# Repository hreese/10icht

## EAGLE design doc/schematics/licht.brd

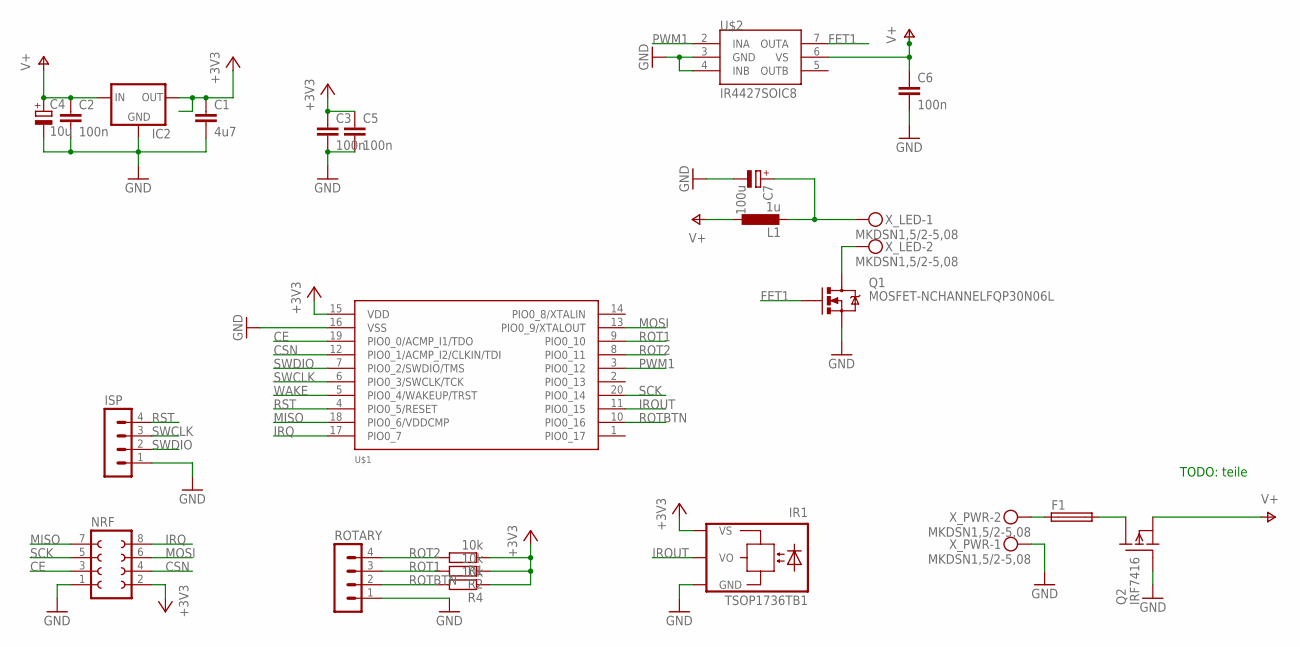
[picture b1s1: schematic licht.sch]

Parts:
C1: 4u7; C0805
C2, C3, C5, C6: 100n; C0805
C4: 10u; E2,5-6
C7: 100u; E2,5-5
F1: PTF45
IC2: TS2940; TO252
IR1: TSOP1736TB1; TSOP17_TB1
ISP: MA04-1
L1: 1u; PISR-BIGPAD
NRF: FE04-2
Q1: MOSFET-NCHANNELFQP30N06L; TO220V
Q2: IRF7416; SO8
R1, R2, R4: 10k; R0805
ROTARY: MA04-1
U$1: LPC812M101JD20; SOIC20WIDE
U$2: IR4427SOIC8; SOIC8
X_LED: MKDSN1,5/2-5,08
X_PWR: MKDSN1,5/2-5,08

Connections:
+3V3: C1.1, C3.1, C5.1, IC2.3 (OUT), IR1.VS, NRF.2, R1.1, R2.1, R4.1, U$1.15 (VDD)
CE: NRF.3, U$1.19 (PIO0_0/ACMP_I1/TDO)
CSN: NRF.4, U$1.12 (PIO0_1/ACMP_I2/CLKIN/TDI)
FET1: Q1.1 (G), U$2.7 (OUTA)
GND: C1.2, C2.2, C3.2, C4.-, C5.2, C6.2, C7.-, IC2.2 (GND), IR1.GND, ISP.1, NRF.1, Q1.3 (S), Q2.4 (G), ROTARY.1, U$1.16 (VSS), U$2.3 (GND), U$2.4 (INB), X_PWR.1
IROUT: IR1.VO, U$1.11 (PIO0_15)
IRQ: NRF.8, U$1.17 (PIO0_7)
MISO: NRF.7, U$1.18 (PIO0_6/VDDCMP)
MOSI: NRF.6, U$1.13 (PIO0_9/XTALOUT)
unnamed: C7.+, L1.2, X_LED.1
unnamed: Q1.2 (D), X_LED.2
unnamed: F1.1, X_PWR.2
unnamed: F1.2, Q2.5 (D), Q2.6 (D), Q2.7 (D), Q2.8 (D)
PWM1: U$1.3 (PIO0_12), U$2.2 (INA)
ROT1: R2.2, ROTARY.3, U$1.9 (PIO0_10)
ROT2: R1.2, ROTARY.4, U$1.8 (PIO0_11)
ROTBTN: R4.2, ROTARY.2, U$1.10 (PIO0_16)
RST: ISP.4, U$1.4 (PIO0_5/RESET)
SCK: NRF.5, U$1.20 (PIO0_14)
SWCLK: ISP.3, U$1.6 (PIO0_3/SWCLK/TCK)
SWDIO: ISP.2, U$1.7 (PIO0_2/SWDIO/TMS)
V+: C2.1, C4.+, C6.1, IC2.1 (IN), L1.1, Q2.1 (S), Q2.2 (S), Q2.3 (S), U$2.6 (VS)
WAKE: U$1.5 (PIO0_4/WAKEUP/TRST)

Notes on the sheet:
TODO: teile

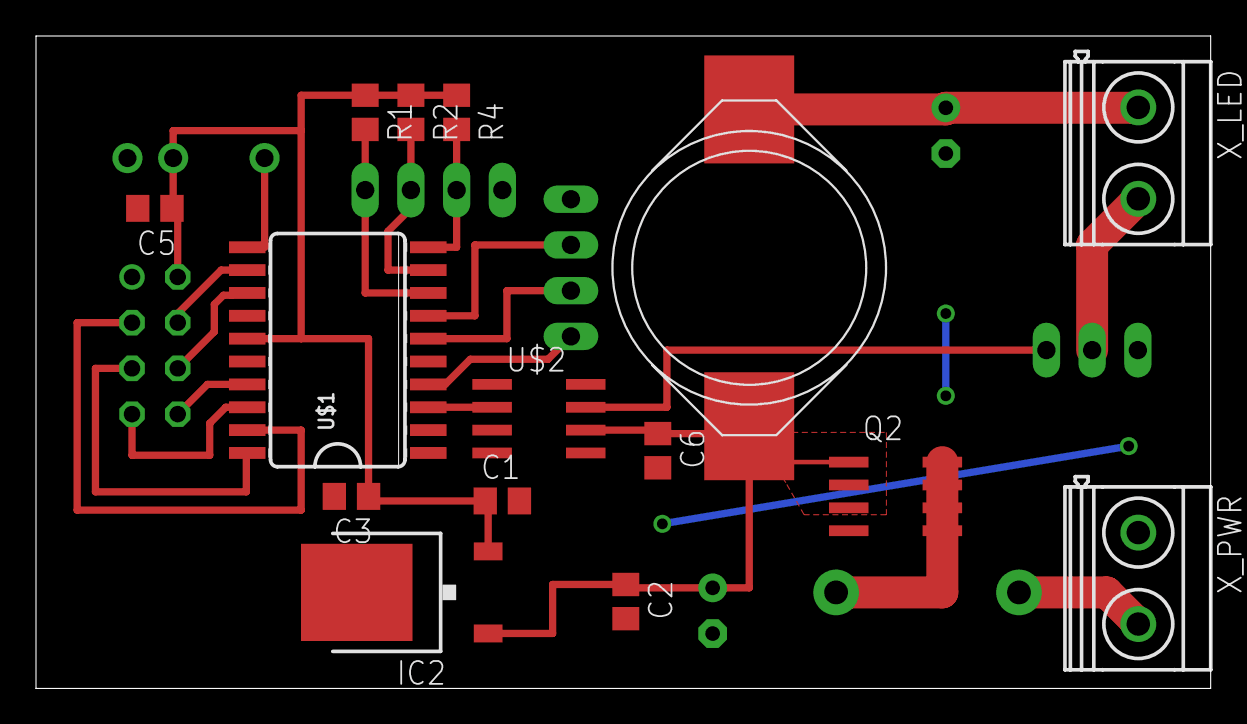
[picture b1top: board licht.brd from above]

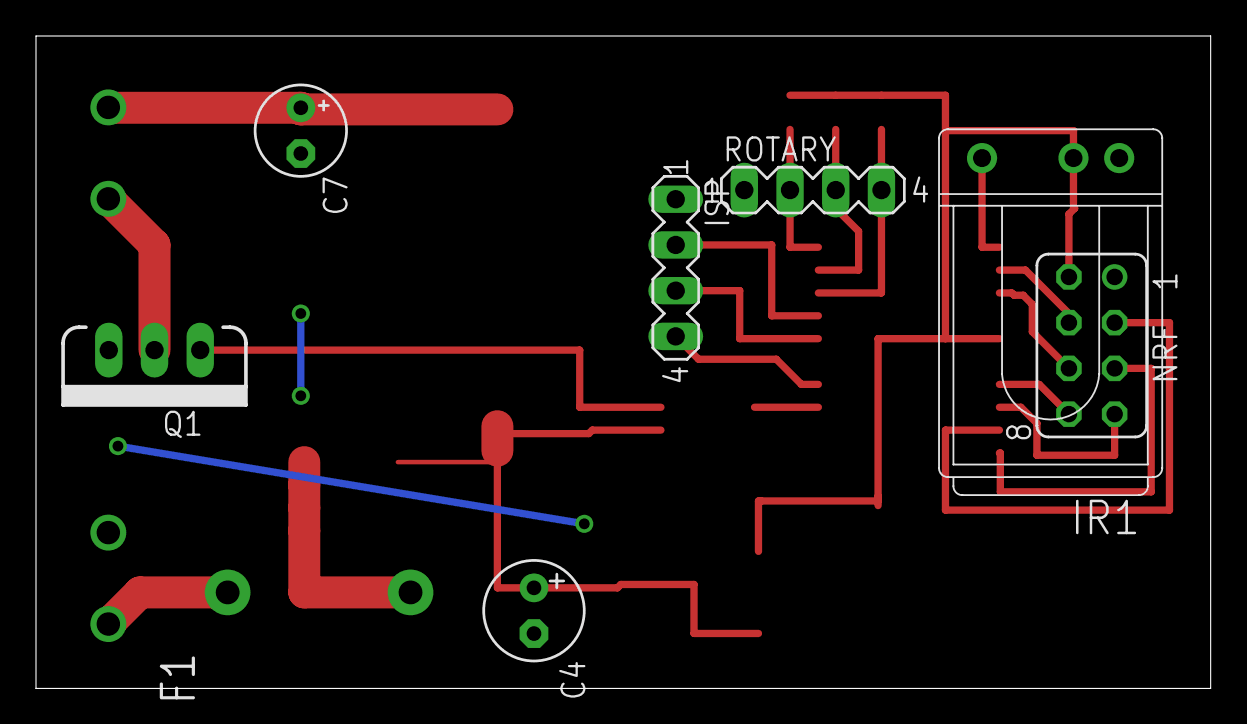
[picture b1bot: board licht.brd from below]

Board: 2 copper layers, 65.3 x 36.2 mm, 23 parts (8 on the bottom side), 22 nets.

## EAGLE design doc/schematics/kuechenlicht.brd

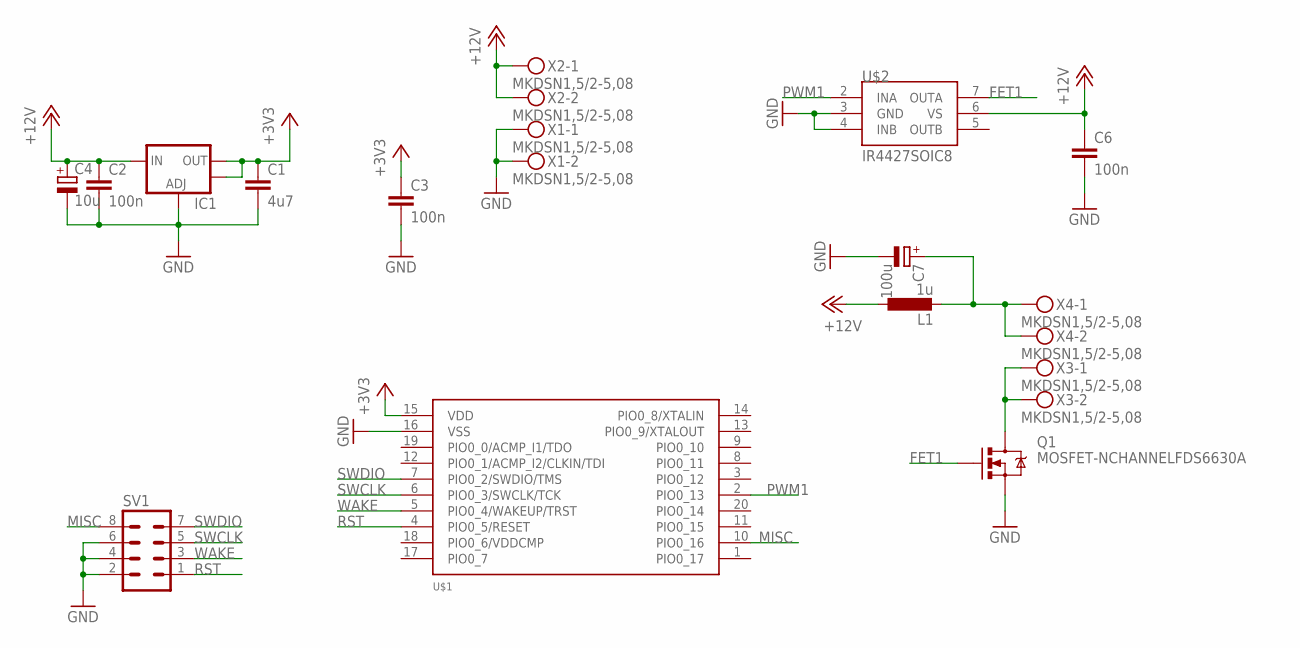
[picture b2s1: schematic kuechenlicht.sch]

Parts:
C1: 4u7; C0805
C2, C3, C6: 100n; C0805
C4: 10u; E2,5-6
C7: 100u; PANASONIC_D-BIGPAD
IC1: V_REG_LM1117SOT223; SOT223
L1: 1u; PISR-BIGPAD
Q1: MOSFET-NCHANNELFDS6630A; SO08
SV1: MA04-2
U$1: LPC812M101JD20; SOIC20WIDE
U$2: IR4427SOIC8; SOIC8
X1, X2, X3, X4: MKDSN1,5/2-5,08

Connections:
+3V3: C1.1, C3.1, IC1.2 (OUT), IC1.4 (OUT), U$1.15 (VDD)
+12V: C2.1, C4.+, C6.1, IC1.3 (IN), L1.1, U$2.6 (VS), X2.1, X2.2
FET1: Q1.4 (G), U$2.7 (OUTA)
GND: C1.2, C2.2, C3.2, C4.-, C6.2, C7.-, IC1.1 (ADJ), Q1.1 (S), Q1.2 (S), Q1.3 (S), SV1.2, SV1.4, SV1.6, U$1.16 (VSS), U$2.3 (GND), U$2.4 (INB), X1.1, X1.2
MISC: SV1.8, U$1.10 (PIO0_16)
unnamed: C7.+, L1.2, X4.1, X4.2
OUT: Q1.5 (D), Q1.6 (D), Q1.7 (D), Q1.8 (D), X3.1, X3.2
PWM1: U$1.2 (PIO0_13), U$2.2 (INA)
RST: SV1.1, U$1.4 (PIO0_5/RESET)
SWCLK: SV1.5, U$1.6 (PIO0_3/SWCLK/TCK)
SWDIO: SV1.7, U$1.7 (PIO0_2/SWDIO/TMS)
WAKE: SV1.3, U$1.5 (PIO0_4/WAKEUP/TRST)

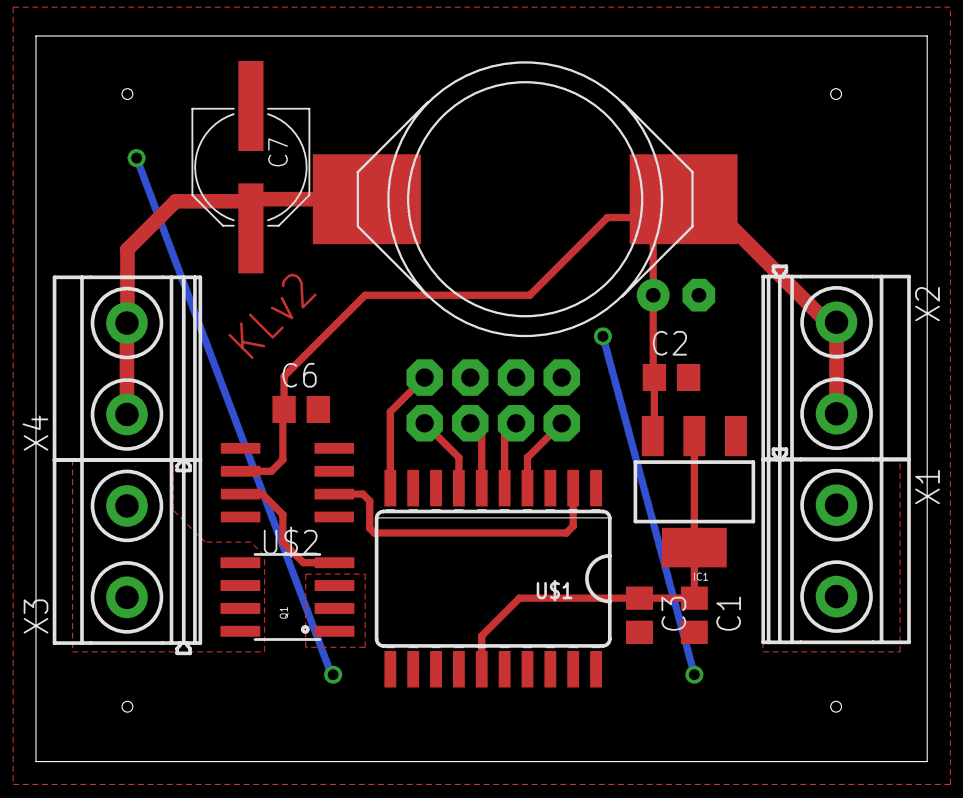
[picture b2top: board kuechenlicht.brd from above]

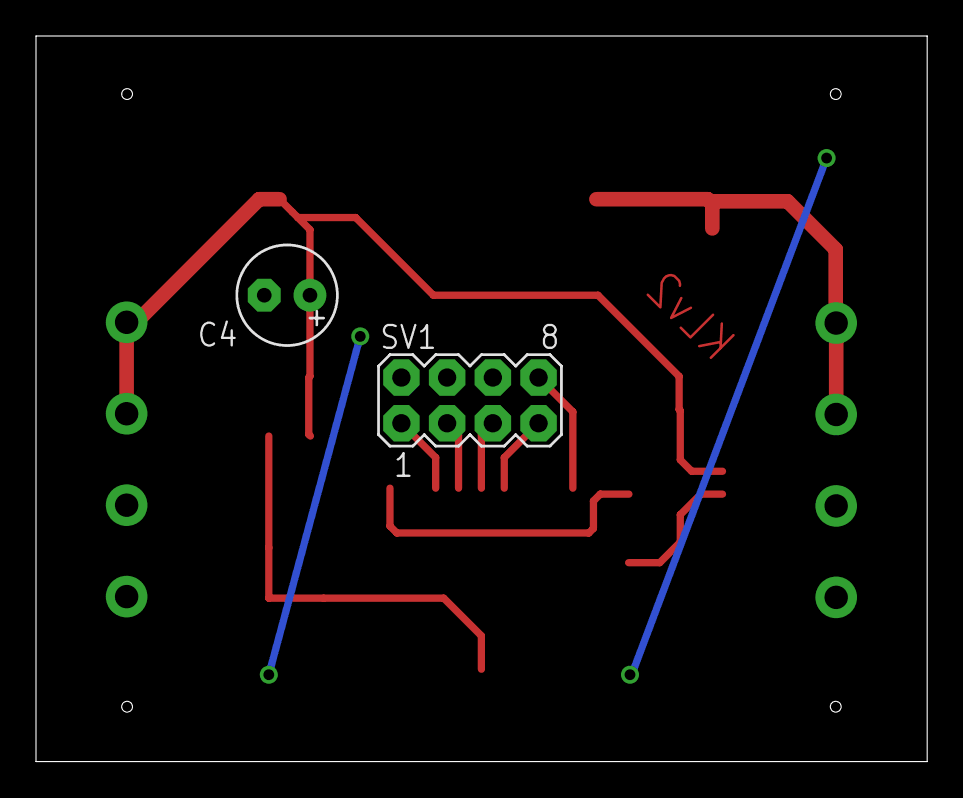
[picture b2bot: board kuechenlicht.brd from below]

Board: 2 copper layers, 49.5 x 40.3 mm, 16 parts (2 on the bottom side), 12 nets.

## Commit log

2014-09-02 initial release
2014-09-02 add license
2014-09-04 debounce switch input
2014-09-11 add long timeout mode, with lots of gotos and magic constants
2014-09-27 Switched layout and board.
2014-09-27 External memory…
2014-09-28 +Verpolungsschutz
2014-09-28 pinheader geändert, reichelt-kompatiblen sicherungshalter
2014-09-28 toller state
2014-09-28 fast fertig
2014-09-29 Lauter neue Teile
2015-02-01 Added datasheet for LEDs.
2015-02-22 pwm tut rudimentär
2015-02-22 hurrah! (Andi)
2015-02-23 more steps
2015-02-23 Added note for one-step-flash

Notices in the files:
parts and their libraries:
SparkFun-PowerIC: Licensing: Creative Commons ShareAlike 4.0 International - https://creativecommons.org/licenses/by-sa/4.0
SparkFun-DiscreteSemi: Licensing: CC v3.0 Share-Alike You are welcome to use this library for commercial purposes.
